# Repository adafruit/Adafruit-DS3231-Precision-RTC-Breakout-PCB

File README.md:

## Adafruit DS3231 Precision RTC Breakout PCB
<a href="http://www.adafruit.com/products/5188"><br/>
Click here to purchase one from the Adafruit shop</a><br/>
<a href="http://www.adafruit.com/products/3013"><br/>
Click here to purchase one from the Adafruit shop</a>

The datasheet for the DS3231 explains that this part is an "Extremely Accurate I²C-Integrated RTC/TCXO/Crystal". And, hey, it does exactly what it says on the tin! This Real Time Clock (RTC) is the most precise you can get in a small, low power package.

Most RTCs use an external 32kHz timing crystal that is used to keep time with low current draw. And that's all well and good, but those crystals have slight drift, particularly when the temperature changes (the temperature changes the oscillation frequency very very very slightly but it does add up!) This RTC is in a beefy package because the crystal is inside the chip! And right next to the integrated crystal is a temperature sensor. That sensor compensates for the frequency changes by adding or removing clock ticks so that the timekeeping stays on schedule.

This is the finest RTC you can get, and now we have it in a compact, breadboard-friendly breakout. With a coin cell plugged into the back, you can get years of precision timekeeping, even when main power is lost. Great for datalogging and clocks, or anything where you need to really know the time.

PCB files for the Adafruit DS3231 Precision RTC Breakout. The format is EagleCAD schematic and board layout
- https://www.adafruit.com/products/3013

### License

Adafruit invests time and resources providing this open source design, please support Adafruit and open-source hardware by purchasing products from [Adafruit](https://www.adafruit.com)!

All text above must be included in any redistribution

Designed by Limor Fried/Ladyada for Adafruit Industries.
Creative Commons Attribution/Share-Alike, all text above must be included in any redistribution. 
See license.txt for additional information.

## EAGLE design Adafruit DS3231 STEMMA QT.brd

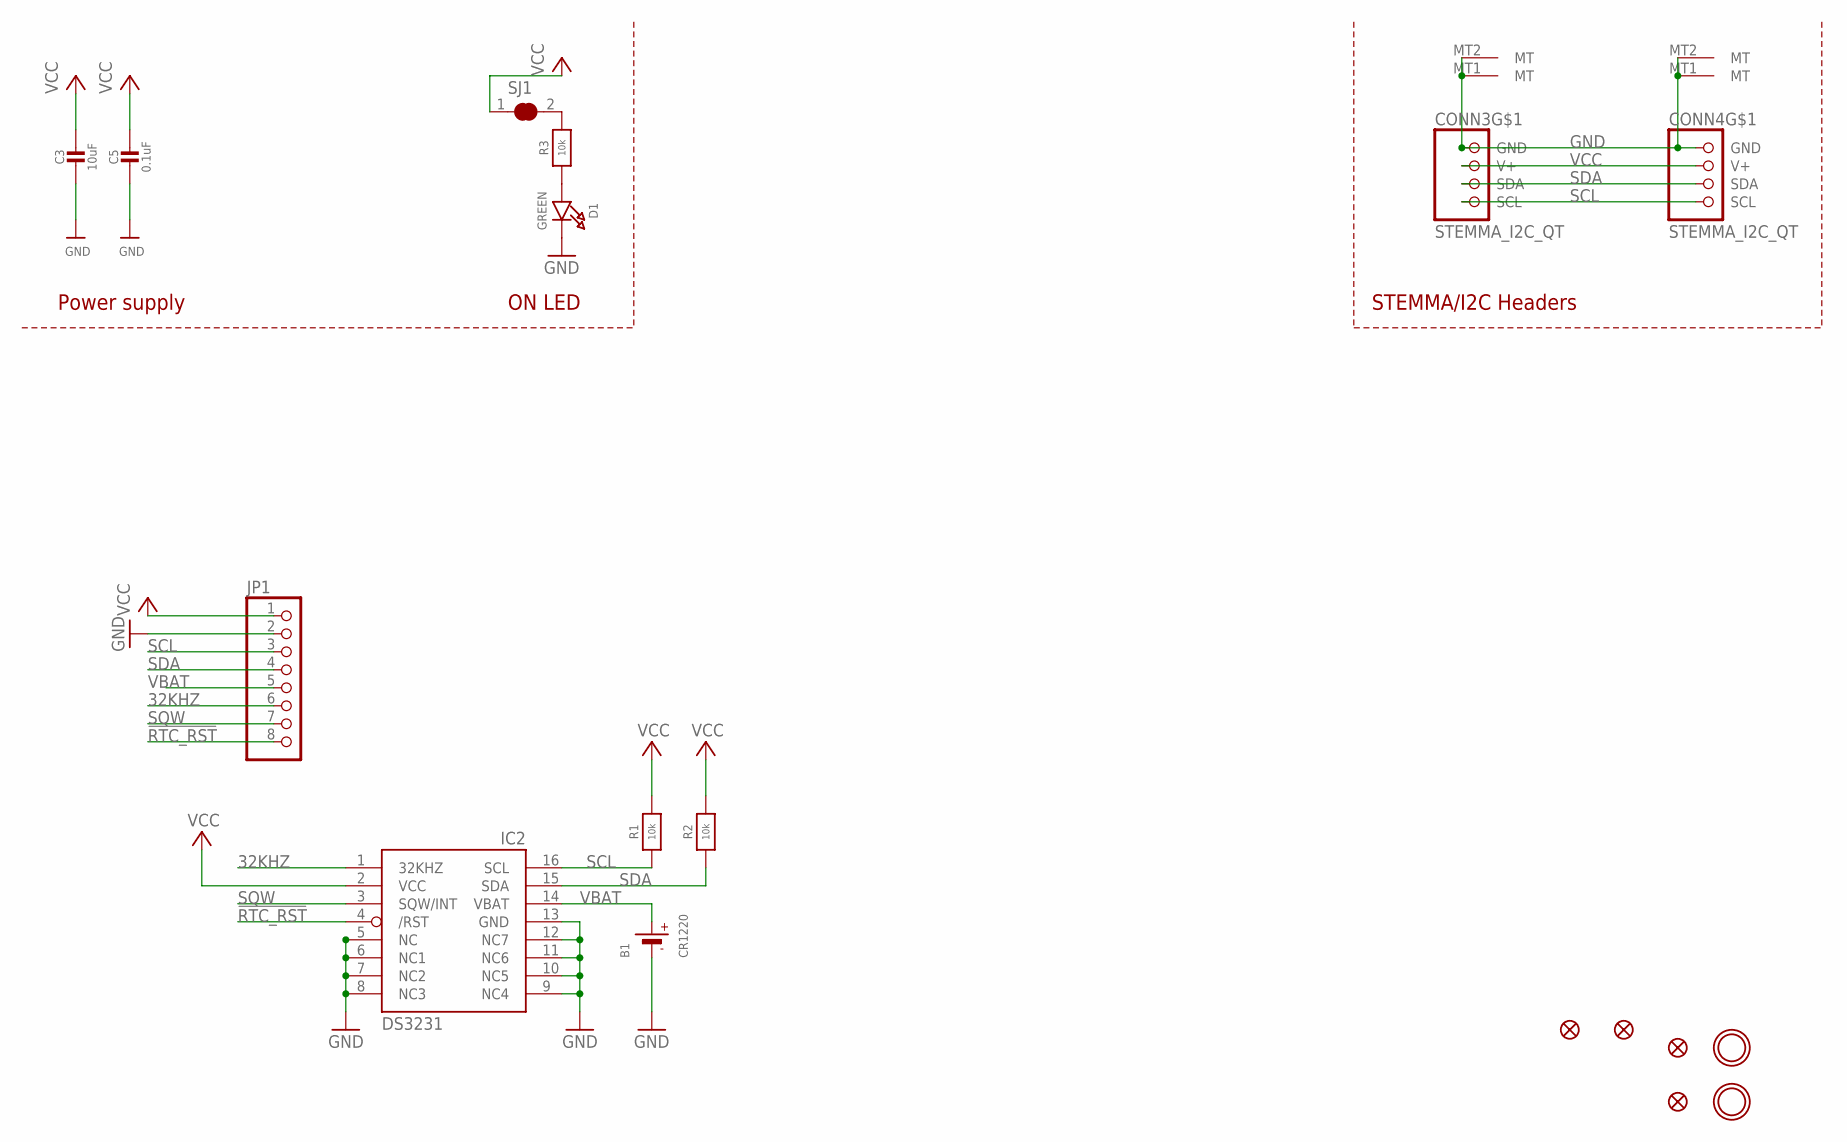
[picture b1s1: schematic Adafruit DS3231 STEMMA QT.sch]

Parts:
B1: CR1220
C3: 10uF; 0805-NO
C5: 0.1uF; 0603-NO
CONN3, CONN4: STEMMA_I2C_QT; JST_SH4
D1: GREEN; CHIPLED_0603_NOOUTLINE
FID1, FID2, FID3, FID4: FIDUCIAL_1MM
IC2: DS3231/SO; SO16W
JP1: HEADER-1X870MIL; 1X08_ROUND_70
R1, R2, R3: 10k; 0603-NO
SJ1: SOLDERJUMPER_CLOSED; SOLDERJUMPER_CLOSEDWIRE
U$9, U$17: MOUNTINGHOLE3.0THIN; MOUNTINGHOLE_3.0_PLATEDTHIN

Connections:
32KHZ: IC2.1 (32KHZ), JP1.6
!RTC_RST: IC2.4 (/RST), JP1.8
GND: B1.-, C3.2, C5.2, CONN3.1 (GND), CONN3.MT1 (MT), CONN3.MT2 (MT), CONN4.1 (GND), CONN4.MT1 (MT), CONN4.MT2 (MT), D1.C, IC2.5 (NC), IC2.6 (NC1), IC2.7 (NC2), IC2.8 (NC3), IC2.9 (NC4), IC2.10 (NC5), IC2.11 (NC6), IC2.12 (NC7), IC2.13 (GND), JP1.2
unnamed: R3.2, SJ1.2
unnamed: D1.A, R3.1
SCL: CONN3.4 (SCL), CONN4.4 (SCL), IC2.16 (SCL), JP1.3, R1.1
SDA: CONN3.3 (SDA), CONN4.3 (SDA), IC2.15 (SDA), JP1.4, R2.1
SQW: IC2.3 (SQW/INT), JP1.7
VBAT: B1.+$1 (+), B1.+$2 (+), IC2.14 (VBAT), JP1.5
VCC: C3.1, C5.1, CONN3.2 (V+), CONN4.2 (V+), IC2.2 (VCC), JP1.1, R1.2, R2.2, SJ1.1

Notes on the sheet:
STEMMA/I2C Headers
ON LED
Power supply

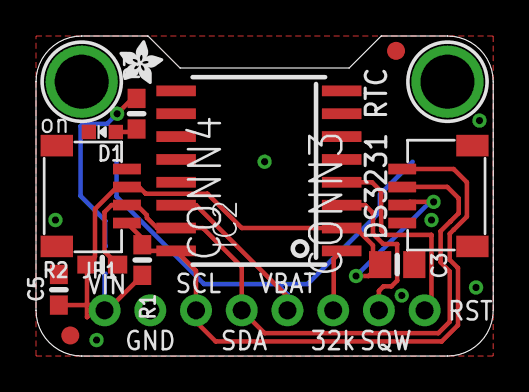
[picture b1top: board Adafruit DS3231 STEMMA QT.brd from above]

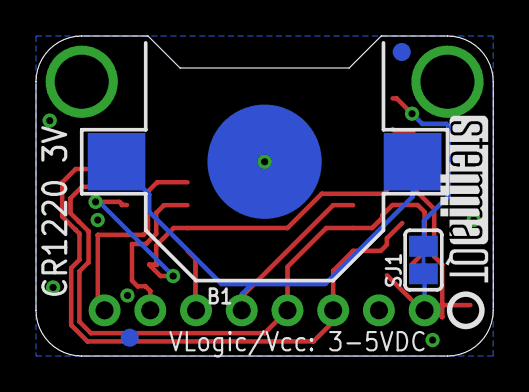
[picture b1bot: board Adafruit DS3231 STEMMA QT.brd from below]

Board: 2 copper layers, 25.4 x 17.8 mm, 21 parts (6 on the bottom side), 10 nets.

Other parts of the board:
U$1: ADAFRUIT_2.5MM
U$25: PCBFEAT-REV-040
U$31: STEMMAQT

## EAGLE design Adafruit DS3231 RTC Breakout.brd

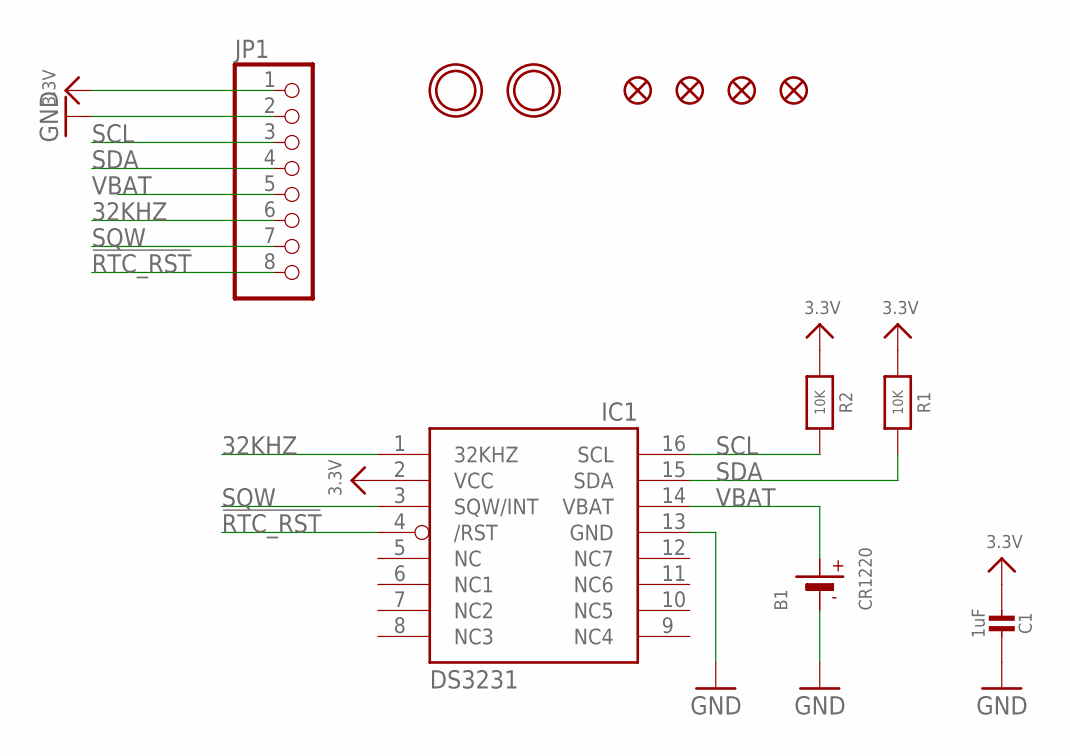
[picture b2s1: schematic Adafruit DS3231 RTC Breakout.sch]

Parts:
B1: CR1220
C1: 1uF; 0805-NO
FID1, FID2, FID3, FID4: FIDUCIAL""; FIDUCIAL_1MM
IC1: DS3231/SO; SO16W
JP1: HEADER-1X870MIL; 1X08_ROUND_70
R1, R2: 10K; 0805-NO
U$6, U$7: MOUNTINGHOLE2.5; MOUNTINGHOLE_2.5_PLATED

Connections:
3.3V: C1.2, IC1.2 (VCC), JP1.1, R1.1, R2.1
32KHZ: IC1.1 (32KHZ), JP1.6
!RTC_RST: IC1.4 (/RST), JP1.8
GND: B1.-, C1.1, IC1.13 (GND), JP1.2
SCL: IC1.16 (SCL), JP1.3, R2.2
SDA: IC1.15 (SDA), JP1.4, R1.2
SQW: IC1.3 (SQW/INT), JP1.7
VBAT: B1.+$1 (+), IC1.14 (VBAT), JP1.5

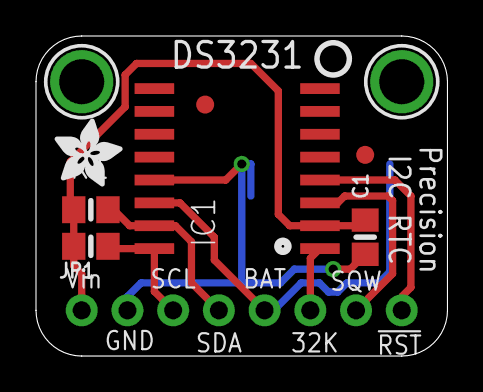
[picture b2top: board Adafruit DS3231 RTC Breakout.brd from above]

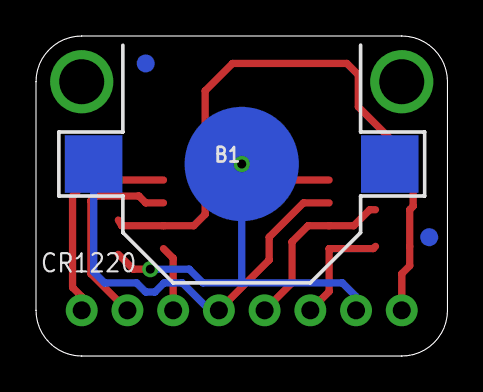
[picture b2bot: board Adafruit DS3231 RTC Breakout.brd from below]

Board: 2 copper layers, 22.9 x 17.8 mm, 14 parts (3 on the bottom side), 8 nets.

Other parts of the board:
U$8: ADAFRUIT_3.5MM
U$9: PCBFEAT-REV-040

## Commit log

2016-06-19 initoriffic
2021-08-04 Add board files.
2021-08-04 Add asset

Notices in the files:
parts and their libraries:
microbuilder: This work is placed in the public domain, and may be freely used for commercial and non-commercial work with the following conditions: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
